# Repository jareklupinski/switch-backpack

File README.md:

# switch-backpack
A small board that makes it easy to tidily wire a homemade keyboard

I wanted to experiment with a variety of keyswitch layouts using the same switches, and didn't want to have flying diode leads everywhere.

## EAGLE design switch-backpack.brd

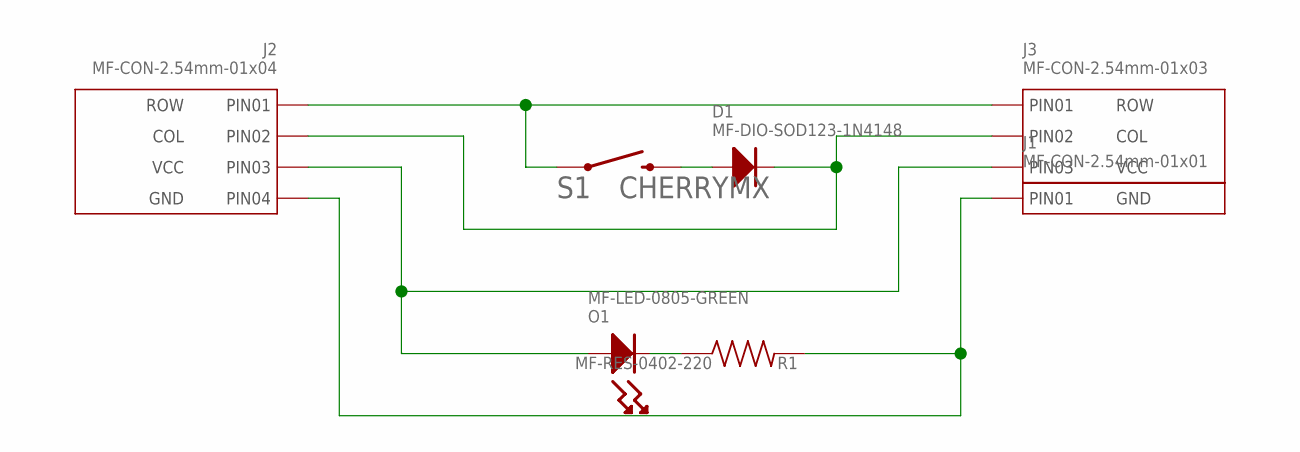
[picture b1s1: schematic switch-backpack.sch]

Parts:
D1: MF-DIO-SOD123-1N4148; SOD-123
J1: MF-CON-2.54mm-01x01; PTH_2.54MM_01X01
J2: MF-CON-2.54mm-01x04; PTH_2.54MM_01X04
J3: MF-CON-2.54mm-01x03; PTH_2.54MM_01X03
O1: MF-LED-0805-GREEN; LED0805
R1: MF-RES-0402-220; R0402
S1: CHERRYMX

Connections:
GND: J1.P$1, J2.P$4 (PIN4), R1.P$2
unnamed: J2.P$1 (PIN1), J3.P$1 (PIN1), S1.P$1 (1)
unnamed: D1.ANODE, S1.P$2 (2)
unnamed: D1.CATHODE, J2.P$2 (PIN2), J3.P$2 (PIN2)
unnamed: O1.CATHODE, R1.P$1
VCC: J2.P$3 (PIN3), J3.P$3 (PIN3), O1.ANODE

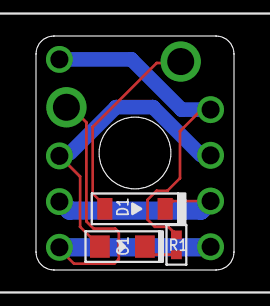
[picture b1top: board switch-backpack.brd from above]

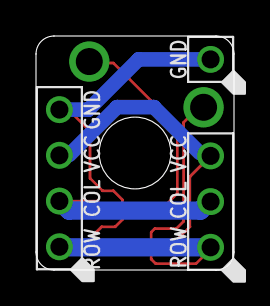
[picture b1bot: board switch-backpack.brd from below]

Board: 2 copper layers, 11.0 x 13.0 mm, 7 parts (3 on the bottom side), 6 nets.

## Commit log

2018-07-05 design tested: working
